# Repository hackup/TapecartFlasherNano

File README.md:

# TapecartFlasher Nano

This is a shield for Arduino Nano and compatible boards to be used with the software from the [TapecartFlasher project](https://github.com/detlefgerhardt/TapecartFlasher). It allows fast and easy transfer of data from a PC or a connected micro SD card to a [Tapecart](https://github.com/ikorb/tapecart) device. More details are available on [hackup.net](https://www.hackup.net/tag/tapecartflasher/).

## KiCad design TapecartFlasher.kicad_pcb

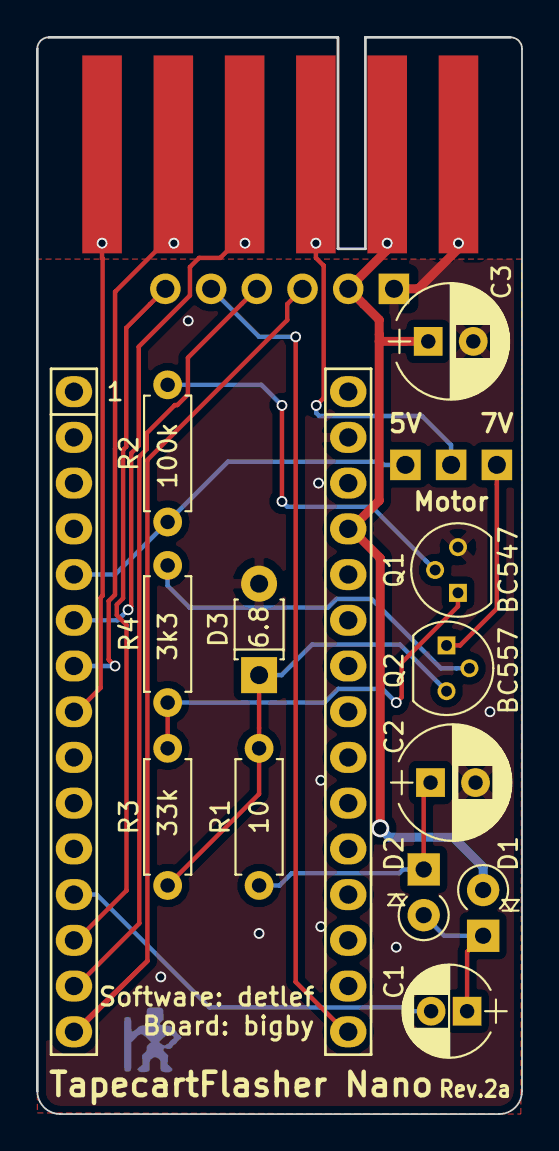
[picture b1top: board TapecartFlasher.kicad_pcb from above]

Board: 2 copper layers, 26.9 x 59.8 mm, 17 parts (1 on the bottom side), 19 nets.

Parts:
C1: 10µ; CP_Radial_D5.0mm_P2.00mm
C2: 100µ; CP_Radial_D6.3mm_P2.50mm
C3: 220µ; CP_Radial_D6.3mm_P2.50mm
D1, D2: 1N5817; D_A-405_P2.54mm_Vertical_KathodeUp
D3: 6.8; D_T-1_P5.08mm_Horizontal
J1: C64-CassettePort; C64-Cassette-Port-Male
J2: SD Module; Socket_Strip_Angled_1x06_Pitch2.54mm
JP1: Vmotor; Pin_Header_Straight_1x03_Pitch2.54mm
P1: Digital; Socket_Strip_Arduino_1x15
P2: Analog; Socket_Strip_Arduino_1x15
Q1: BC547; TO-92_Molded_Narrow
Q2: BC557; TO-92_Molded_Narrow
R1: 10; R_Axial_DIN0207_L6.3mm_D2.5mm_P7.62mm_Horizontal
R2: 100k; R_Axial_DIN0207_L6.3mm_D2.5mm_P7.62mm_Horizontal
R3: 33k; R_Axial_DIN0207_L6.3mm_D2.5mm_P7.62mm_Horizontal
R4: 3k3; R_Axial_DIN0207_L6.3mm_D2.5mm_P7.62mm_Horizontal

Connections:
+5V: C3.1, D1.2, J1.2, J1.B, J2.2, P2.4
GND: C2.2, C3.2, D3.2, J1.1, J1.A, J2.1, P1.4, P2.2, Q1.3
Motor5: JP1.1, P1.5, R2.2
Motor7: JP1.3, Q2.1
unnamed: C1.1, D1.1, D2.2
unnamed: C2.1, D2.1, R1.1
unnamed: J1.3, J1.C, JP1.2
unnamed: Q1.1, R3.2, R4.2
unnamed: Q1.2, R2.1
unnamed: Q2.2, R4.1
PWM: C1.2, P1.12
Read: J1.4, J1.D, P1.6
SD_MISO: J2.3, P1.15
SD_MOSI: J2.4, P1.14
SD_SCK: J2.5, P2.15
SD_SEL: J2.6, P1.13
Sense: J1.6, J1.F, P1.8
VPP: D3.1, Q2.3, R1.2, R3.1
Write: J1.5, J1.E, P1.7

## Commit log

2018-08-26 Initial commit.
2018-08-26 Added SD module connector and motor voltage jumper.
2018-08-26 Renamed board.
2018-08-27 Preparing for Gerber export.
2018-08-27 Finialized revision 1.
2018-08-27 Project address should have been on there.
2018-09-04 Added URL to silk screen.
2018-09-04 Annotated schematics.
2018-09-04 Changed resistor footprints.
2018-09-06 Modified/corrected zender diode circuit.
2018-10-23 Added decoupling capacitor to prevent Arduino from rebooting.
2018-10-24 Fixed gold fingers.
2018-12-04 Moved switch labels.
2018-12-04 Added readme file.
2018-12-05 Updated Tapecart URL.
2018-12-12 Use local 3D model for socket strips that allow export to STEP.
2019-01-19 Added PDF export of the schematics.
